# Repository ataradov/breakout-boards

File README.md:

## Breakout Boards

This is a collection of random breakout boards I developed to get started with a new device.

Firmware for the SAM D11 used as a debugger/VCP interface on some boards is available [here](https://github.com/ataradov/free-dap))

### Currrently available boards:

* Atmel SAME70 / SAMS70
* ST STM32G071
* GigaDevice GD32F407V (will probably work for STM32F407 as well)
* Lattice LCMXO256C
* Lattice LCMXO2-2000HC
* Nuvoton M484SIDAE
* Atmel SAMD11 USB Test Board
* Atmel SAMD11 Nano - full breakout with USB connector
* Raspberry Pi RP2040
* Gowin GW1N-UV9QN48

### Errata

The boards are added here at the same time they are submitted for fabrication. There may be issues with them,
but I will not know about them until the boards arrive. Those issues will not be fixed in the files, unless
the boards are really broken and I need to reorder them, or I want to reorder them for some other reason.

Below is a list of known issues:
1. GD32F407V - BOOT0 (pin 94) should be pulled down by a 10 kOhm resistor. This is an easy fix, there is a groud pour near the jumper.
2. SAMD11 USB Test Board - Switch footprint is slightly off (mounting pads are wider than on a real switch).

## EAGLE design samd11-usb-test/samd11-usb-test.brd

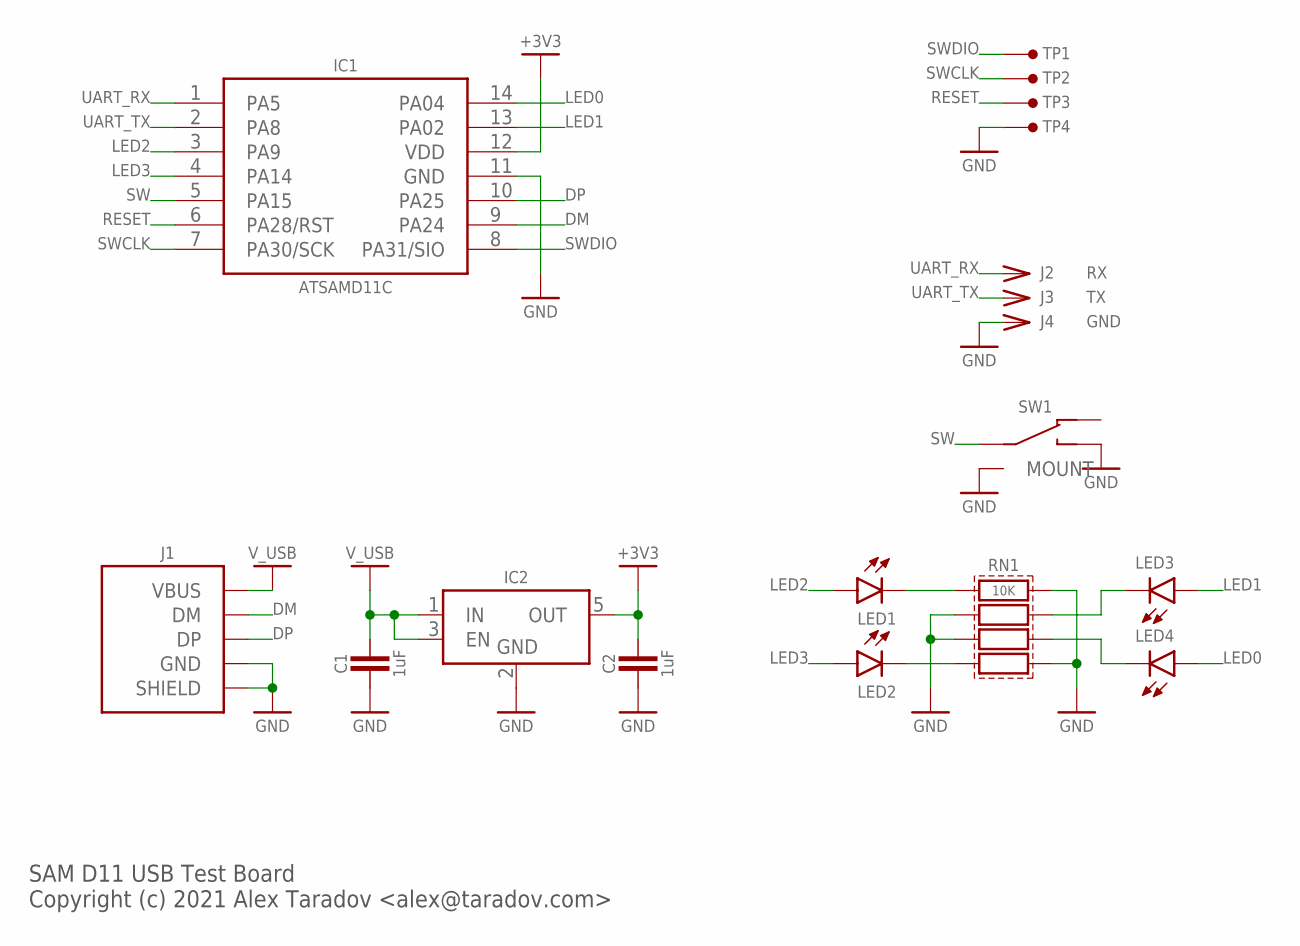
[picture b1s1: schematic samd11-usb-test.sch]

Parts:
C1, C2: 1uF; SMD0603
IC1: ATSAMD11C; SO-14
IC2: MIC5504-SOT23-5; SOT23-5
J1: USB-A-PLUG-TH-NM
J2: RX; PIN-TH
J3: TX; PIN-TH
J4: GND; PIN-TH
LED1, LED2, LED3, LED4: LED_SMDLED_0603; SMD0603
RN1: 10K; SMD0603-X4
SW1: SPDT_SWITCH-MOUNT-SMD-MOUNT-NO-HOLES; SPDT-SMD-5MM-NO-HOLES
TP1, TP2, TP3, TP4: TEST-POINT-1.27MM-TH; TP-1.27MM-TH

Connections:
+3V3: C2.2, IC1.12 (VDD), IC2.5 (OUT)
DM: IC1.9 (PA24), J1.2 (DM)
DP: IC1.10 (PA25), J1.3 (DP)
GND: C1.1, C2.1, IC1.11 (GND), IC2.2 (GND), J1.4 (GND), J1.M1 (SHIELD), J1.M2 (SHIELD), J4.1, RN1.2, RN1.3, RN1.5, RN1.8, SW1.B, SW1.M0 (MOUNT), SW1.M1 (MOUNT), SW1.M2 (MOUNT), SW1.M3 (MOUNT), TP4.1
LED0: IC1.14 (PA04), LED4.1 (A)
LED1: IC1.13 (PA02), LED3.1 (A)
LED2: IC1.3 (PA9), LED1.1 (A)
LED3: IC1.4 (PA14), LED2.1 (A)
unnamed: LED2.2 (C), RN1.4
unnamed: LED1.2 (C), RN1.1
unnamed: LED3.2 (C), RN1.7
unnamed: LED4.2 (C), RN1.6
RESET: IC1.6 (PA28/RST), TP3.1
SW: IC1.5 (PA15), SW1.C
SWCLK: IC1.7 (PA30/SCK), TP2.1
SWDIO: IC1.8 (PA31/SIO), TP1.1
UART_RX: IC1.1 (PA5), J2.1
UART_TX: IC1.2 (PA8), J3.1
V_USB: C1.2, IC2.1 (IN), IC2.3 (EN), J1.1 (VBUS)

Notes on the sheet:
SAM D11 USB Test Board Copyright (c) 2021 Alex Taradov <alex@taradov.com>

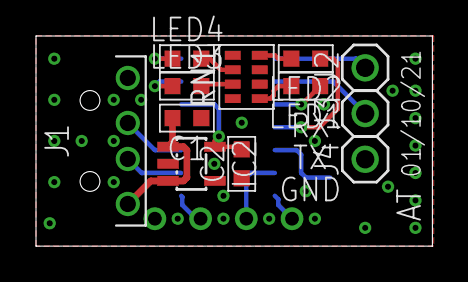
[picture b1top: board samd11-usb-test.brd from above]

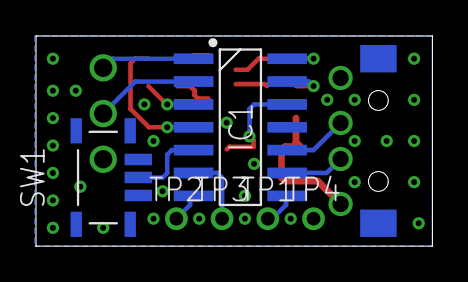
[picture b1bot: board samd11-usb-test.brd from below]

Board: 2 copper layers, 22.0 x 11.7 mm, 18 parts (6 on the bottom side), 19 nets.

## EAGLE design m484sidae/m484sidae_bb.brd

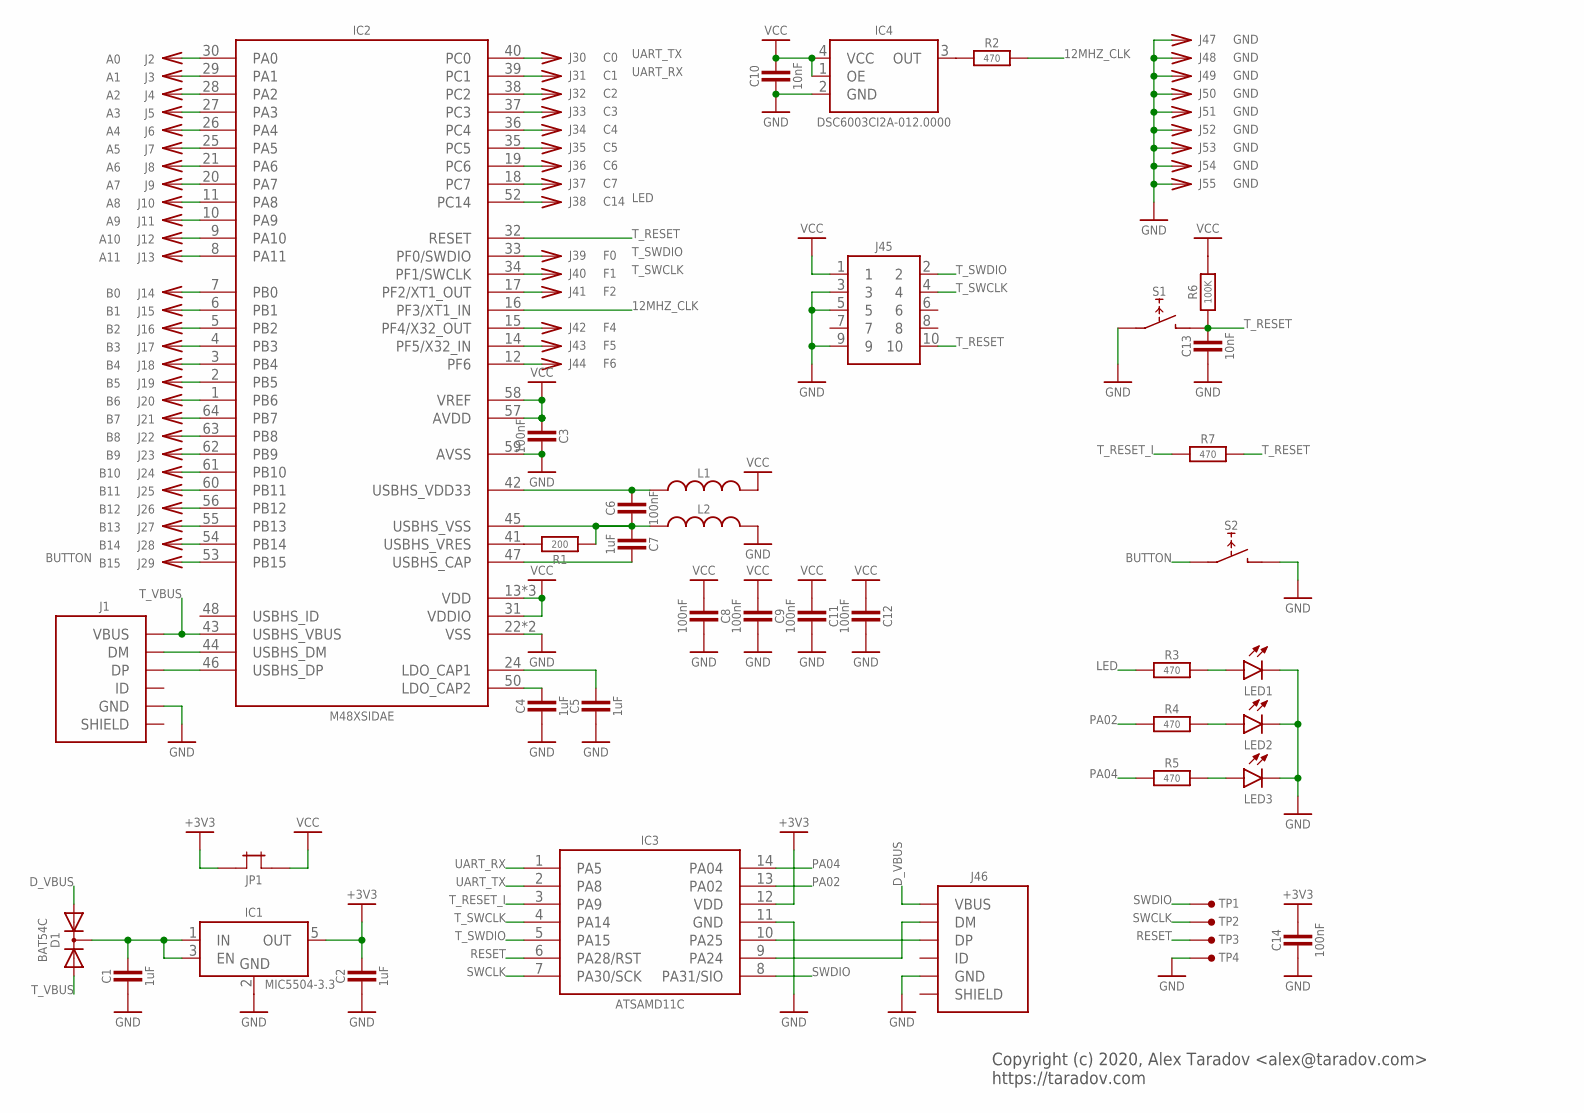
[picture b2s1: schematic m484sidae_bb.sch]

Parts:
C1, C2, C4, C5, C7: 1uF; SMD0603
C3, C6, C8, C9, C11, C12, C14: 100nF; SMD0603
C10, C13: 10nF; SMD0603
D1: BAT54C; SOT23
IC1: MIC5504-3.3; SOT23-5
IC2: M48XSIDAE; TQFP-64-0.4MM
IC3: ATSAMD11C; SO-14
IC4: DSC6003CI2A-012.0000; CDFN4
J1, J46: USB-B-MICRO-SMT; USB-B-MICRO-SMT-SHELL-TH
J2: A0; PIN-TH
J3: A1; PIN-TH
J4: A2; PIN-TH
J5: A3; PIN-TH
J6: A4; PIN-TH
J7: A5; PIN-TH
J8: A6; PIN-TH
J9: A7; PIN-TH
J10: A8; PIN-TH
J11: A9; PIN-TH
J12: A10; PIN-TH
J13: A11; PIN-TH
J14: B0; PIN-TH
J15: B1; PIN-TH
J16: B2; PIN-TH
J17: B3; PIN-TH
J18: B4; PIN-TH
J19: B5; PIN-TH
J20: B6; PIN-TH
J21: B7; PIN-TH
J22: B8; PIN-TH
J23: B9; PIN-TH
J24: B10; PIN-TH
J25: B11; PIN-TH
J26: B12; PIN-TH
J27: B13; PIN-TH
J28: B14; PIN-TH
J29: B15; PIN-TH
J30: C0; PIN-TH
J31: C1; PIN-TH
J32: C2; PIN-TH
J33: C3; PIN-TH
J34: C4; PIN-TH
J35: C5; PIN-TH
J36: C6; PIN-TH
J37: C7; PIN-TH
J38: C14; PIN-TH
J39: F0; PIN-TH
J40: F1; PIN-TH
J41: F2; PIN-TH
J42: F4; PIN-TH
J43: F5; PIN-TH
J44: F6; PIN-TH
J45: HEADER-5X2-TH-1.27; HEADER-5X2-1.27MM
J47, J48, J49, J50, J51, J52, J53, J54, J55: GND; PIN-TH
JP1: JUMPER-TH-TH; JUMPER-TH
L1, L2: L-0603; SMD0603
LED1, LED2, LED3: LED_SMDLED_0603; SMD0603
R1: 200; SMD0603
R2, R3, R4, R5, R7: 470; SMD0603
R6: 100K; SMD0603
S1, S2: TACT_SWITCH_6MM-SMD-HALF; TACT-SMD-6MM-HALF
TP1: SIO; TP-1.27MM
TP2, TP3, TP4: TEST-POINT-1.27MM; TP-1.27MM

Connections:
12MHZ_CLK: IC2.16 (PF3/XT1_IN), R2.2
+3V3: C2.2, C14.2, IC1.5 (OUT), IC3.12 (VDD), JP1.1
BUTTON: IC2.53 (PB15), J29.1, S2.1
D_VBUS: D1.1 (A1), J46.1 (VBUS)
GND: C1.1, C2.1, C3.2, C4.1, C5.1, C8.2, C9.2, C10.1, C11.2, C12.2, C13.1, C14.1, IC1.2 (GND), IC2.22 (VSS), IC2.49 (VSS), IC2.59 (AVSS), IC3.11 (GND), IC4.2 (GND), J1.5 (GND), J45.3, J45.5, J45.9, J46.5 (GND), J47.1, J48.1, J49.1, J50.1, J51.1, J52.1, J53.1, J54.1, J55.1, L2.2, LED1.2 (C), LED2.2 (C), LED3.2 (C), S1.1, S2.2, TP4.1
IN: C1.2, D1.3 (CC), IC1.1 (IN), IC1.3 (EN)
LED: IC2.52 (PC14), J38.1, R3.1
unnamed: IC3.9 (PA24), J46.2 (DM)
unnamed: IC3.10 (PA25), J46.3 (DP)
unnamed: LED2.1 (A), R4.2
unnamed: IC4.3 (OUT), R2.1
unnamed: LED3.1 (A), R5.2
unnamed: IC2.44 (USBHS_DM), J1.2 (DM)
unnamed: IC2.46 (USBHS_DP), J1.3 (DP)
unnamed: IC2.41 (USBHS_VRES), R1.2
unnamed: C5.2, IC2.24 (LDO_CAP1)
unnamed: C4.2, IC2.50 (LDO_CAP2)
unnamed: LED1.1 (A), R3.2
unnamed: IC2.37 (PC3), J33.1
unnamed: IC2.38 (PC2), J32.1
unnamed: IC2.36 (PC4), J34.1
unnamed: IC2.35 (PC5), J35.1
unnamed: IC2.19 (PC6), J36.1
unnamed: IC2.18 (PC7), J37.1
unnamed: IC2.30 (PA0), J2.1
unnamed: IC2.29 (PA1), J3.1
unnamed: IC2.28 (PA2), J4.1
unnamed: IC2.27 (PA3), J5.1
unnamed: IC2.26 (PA4), J6.1
unnamed: IC2.25 (PA5), J7.1
unnamed: IC2.21 (PA6), J8.1
unnamed: IC2.20 (PA7), J9.1
unnamed: IC2.10 (PA9), J11.1
unnamed: IC2.9 (PA10), J12.1
unnamed: IC2.8 (PA11), J13.1
unnamed: IC2.11 (PA8), J10.1
unnamed: IC2.7 (PB0), J14.1
unnamed: IC2.6 (PB1), J15.1
unnamed: IC2.5 (PB2), J16.1
unnamed: IC2.4 (PB3), J17.1
unnamed: IC2.3 (PB4), J18.1
unnamed: IC2.1 (PB6), J20.1
unnamed: IC2.64 (PB7), J21.1
unnamed: IC2.63 (PB8), J22.1
unnamed: IC2.62 (PB9), J23.1
unnamed: IC2.61 (PB10), J24.1
unnamed: IC2.60 (PB11), J25.1
unnamed: IC2.56 (PB12), J26.1
unnamed: IC2.55 (PB13), J27.1
unnamed: IC2.54 (PB14), J28.1
unnamed: IC2.2 (PB5), J19.1
unnamed: IC2.17 (PF2/XT1_OUT), J41.1
unnamed: IC2.12 (PF6), J44.1
unnamed: IC2.15 (PF4/X32_OUT), J42.1
unnamed: IC2.14 (PF5/X32_IN), J43.1
PA02: IC3.13 (PA02), R4.1
PA04: IC3.14 (PA04), R5.1
RESET: IC3.6 (PA28/RST), TP3.1
SWCLK: IC3.7 (PA30/SCK), TP2.1
SWDIO: IC3.8 (PA31/SIO), TP1.1
T_RESET: C13.2, IC2.32 (RESET), J45.10, R6.1, R7.2, S1.2
T_RESET_I: IC3.3 (PA9), R7.1
T_SWCLK: IC2.34 (PF1/SWCLK), IC3.4 (PA14), J40.1, J45.4
T_SWDIO: IC2.33 (PF0/SWDIO), IC3.5 (PA15), J39.1, J45.2
T_VBUS: D1.2 (A2), IC2.43 (USBHS_VBUS), J1.1 (VBUS)
UART_RX: IC2.39 (PC1), IC3.1 (PA5), J31.1
UART_TX: IC2.40 (PC0), IC3.2 (PA8), J30.1
USBHS_CAP: C7.2, IC2.47 (USBHS_CAP)
USBHS_GND: C6.1, C7.1, IC2.45 (USBHS_VSS), L2.1, R1.1
USBHS_VDD33: C6.2, IC2.42 (USBHS_VDD33), L1.1
VCC: C3.1, C8.1, C9.1, C10.2, C11.1, C12.1, IC2.13 (VDD), IC2.23 (VDD), IC2.31 (VDDIO), IC2.51 (VDD), IC2.57 (AVDD), IC2.58 (VREF), IC4.1 (OE), IC4.4 (VCC), J45.1, JP1.2, L1.2, R6.2

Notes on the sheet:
Copyright (c) 2020, Alex Taradov <alex@taradov.com> https://taradov.com

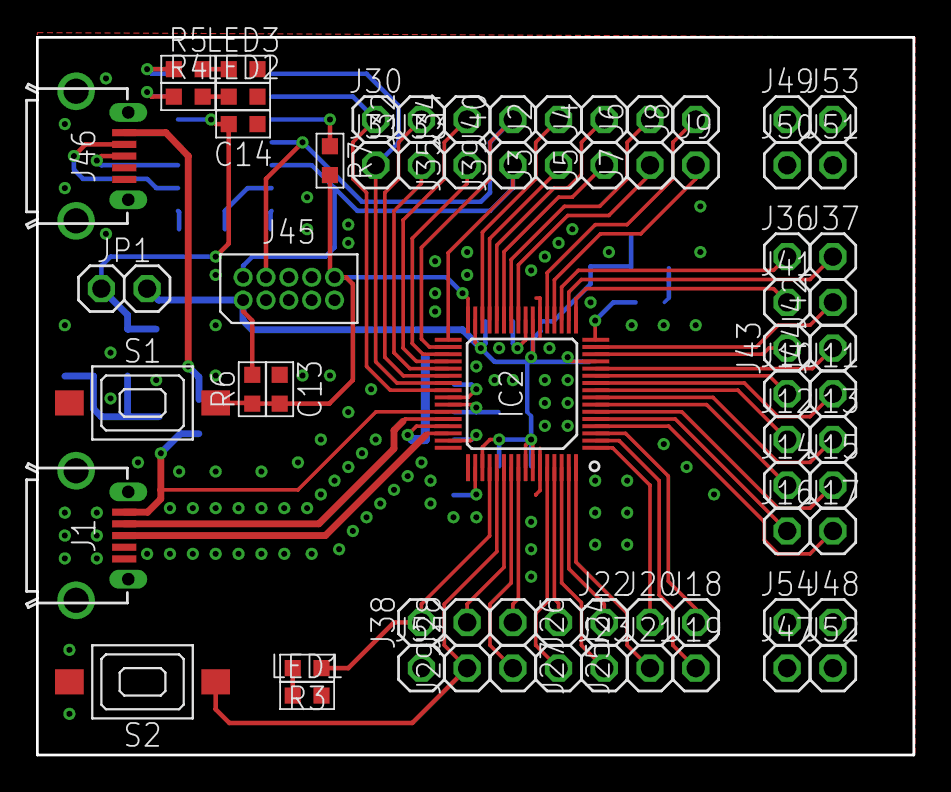
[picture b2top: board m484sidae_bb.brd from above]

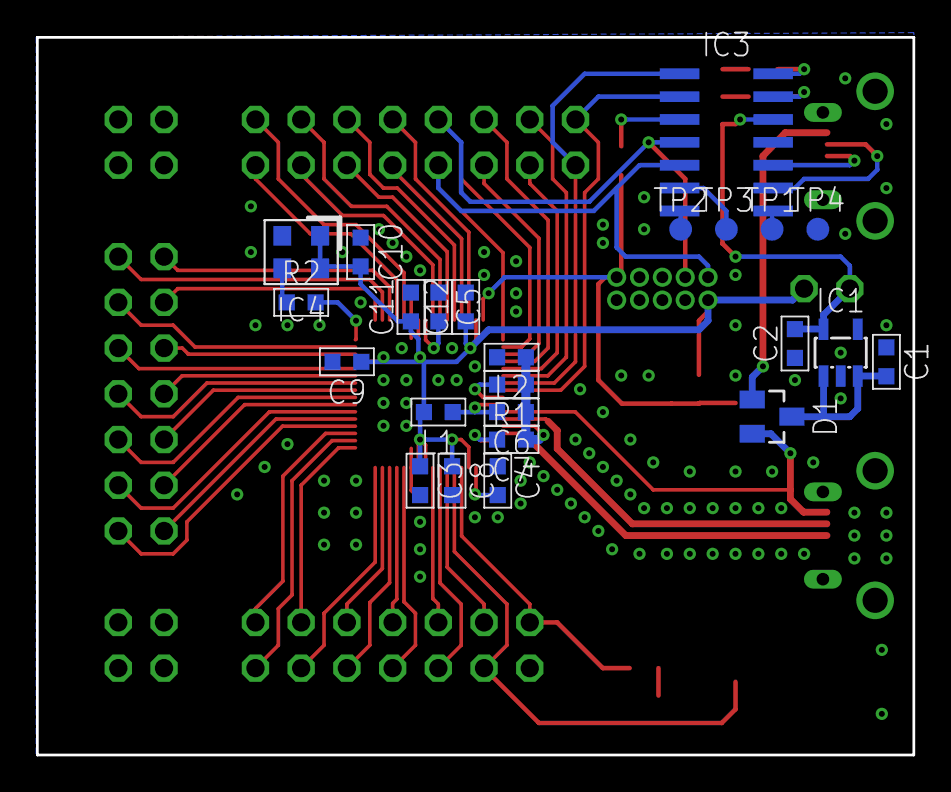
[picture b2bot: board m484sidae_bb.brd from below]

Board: 2 copper layers, 48.7 x 39.9 mm, 93 parts (24 on the bottom side), 71 nets.

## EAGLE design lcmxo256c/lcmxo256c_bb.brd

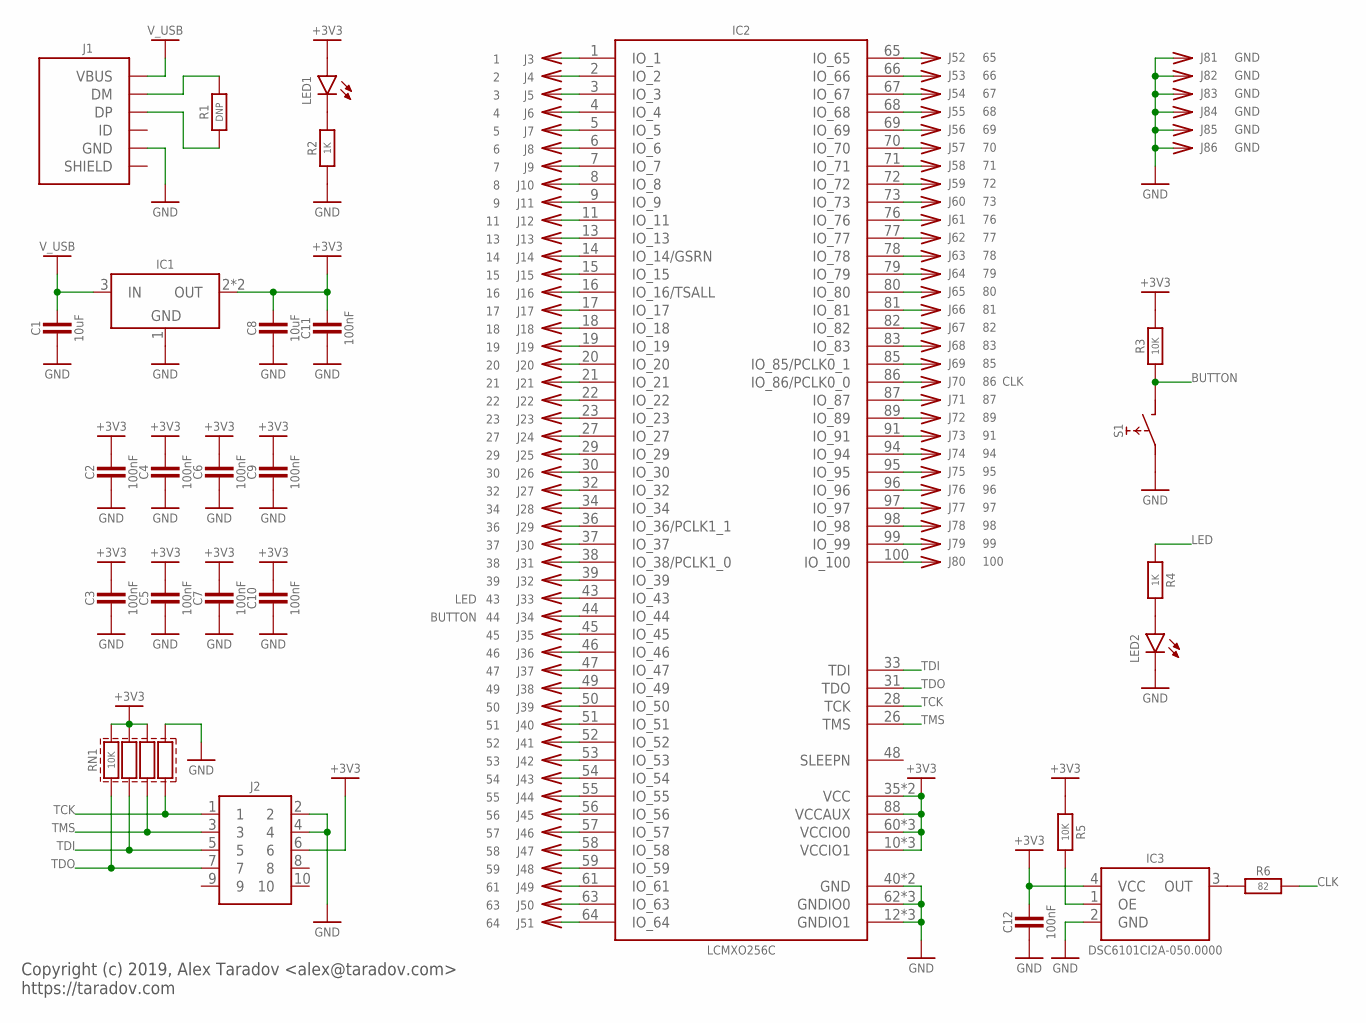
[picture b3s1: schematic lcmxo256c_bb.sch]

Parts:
C1, C8: 10uF; SMD0805
C2, C3, C4, C5, C6, C7, C9, C10, C11, C12: 100nF; SMD0603
IC1: LM1117-SOT223; SOT223
IC2: LCMXO256C; TQFP-100-0.5MM
IC3: DSC6101CI2A-050.0000; CDFN4
J1: USB-B-MICRO-SMT; USB-B-MICRO-SMT-SHELL-TH
J2: HEADER-5X2-TH-1.27; HEADER-5X2-1.27MM
J3: 1; PIN-TH
J4: 2; PIN-TH
J5: 3; PIN-TH
J6: 4; PIN-TH
J7: 5; PIN-TH
J8: 6; PIN-TH
J9: 7; PIN-TH
J10: 8; PIN-TH
J11: 9; PIN-TH
J12: 11; PIN-TH
J13: 13; PIN-TH
J14: 14; PIN-TH
J15: 15; PIN-TH
J16: 16; PIN-TH
J17: 17; PIN-TH
J18: 18; PIN-TH
J19: 19; PIN-TH
J20: 20; PIN-TH
J21: 21; PIN-TH
J22: 22; PIN-TH
J23: 23; PIN-TH
J24: 27; PIN-TH
J25: 29; PIN-TH
J26: 30; PIN-TH
J27: 32; PIN-TH
J28: 34; PIN-TH
J29: 36; PIN-TH
J30: 37; PIN-TH
J31: 38; PIN-TH
J32: 39; PIN-TH
J33: 43; PIN-TH
J34: 44; PIN-TH
J35: 45; PIN-TH
J36: 46; PIN-TH
J37: 47; PIN-TH
J38: 49; PIN-TH
J39: 50; PIN-TH
J40: 51; PIN-TH
J41: 52; PIN-TH
J42: 53; PIN-TH
J43: 54; PIN-TH
J44: 55; PIN-TH
J45: 56; PIN-TH
J46: 57; PIN-TH
J47: 58; PIN-TH
J48: 59; PIN-TH
J49: 61; PIN-TH
J50: 63; PIN-TH
J51: 64; PIN-TH
J52: 65; PIN-TH
J53: 66; PIN-TH
J54: 67; PIN-TH
J55: 68; PIN-TH
J56: 69; PIN-TH
J57: 70; PIN-TH
J58: 71; PIN-TH
J59: 72; PIN-TH
J60: 73; PIN-TH
J61: 76; PIN-TH
J62: 77; PIN-TH
J63: 78; PIN-TH
J64: 79; PIN-TH
J65: 80; PIN-TH
J66: 81; PIN-TH
J67: 82; PIN-TH
J68: 83; PIN-TH
J69: 85; PIN-TH
J70: 86; PIN-TH
J71: 87; PIN-TH
J72: 89; PIN-TH
J73: 91; PIN-TH
J74: 94; PIN-TH
J75: 95; PIN-TH
J76: 96; PIN-TH
J77: 97; PIN-TH
J78: 98; PIN-TH
J79: 99; PIN-TH
J80: 100; PIN-TH
J81, J82, J83, J84, J85, J86: GND; PIN-TH
LED1, LED2: LED_SMDLED_0603; SMD0603
R1: DNP; SMD0603
R2, R4: 1K; SMD0603
R3, R5: 10K; SMD0603
R6: 82; SMD0603
RN1: 10K; SMD0603-X4
S1: TACT_SWITCH_6MM-SMD-HALF; TACT-SMD-6MM-HALF

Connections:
+3V3: C2.2, C3.2, C4.2, C5.2, C6.2, C7.2, C8.2, C9.2, C10.2, C11.2, C12.2, IC1.2 (OUT), IC1.4 (OUT), IC2.10 (VCCIO1), IC2.24 (VCCIO1), IC2.35 (VCC), IC2.41 (VCCIO1), IC2.60 (VCCIO0), IC2.74 (VCCIO0), IC2.88 (VCCAUX), IC2.90 (VCC), IC2.92 (VCCIO0), IC3.4 (VCC), J2.6, LED1.1 (A), R3.2, R5.1, RN1.6, RN1.7, RN1.8
BUTTON: IC2.44 (IO_44), J34.1, R3.1, S1.2
CLK: IC2.86 (IO_86/PCLK0_0), J70.1, R6.2
GND: C1.1, C2.1, C3.1, C4.1, C5.1, C6.1, C7.1, C8.1, C9.1, C10.1, C11.1, C12.1, IC1.1 (GND), IC2.12 (GNDIO1), IC2.25 (GNDIO1), IC2.40 (GND), IC2.42 (GNDIO1), IC2.62 (GNDIO0), IC2.75 (GNDIO0), IC2.84 (GND), IC2.93 (GNDIO0), IC3.2 (GND), J1.5 (GND), J2.2, J2.4, J81.1, J82.1, J83.1, J84.1, J85.1, J86.1, LED2.2 (C), R2.1, RN1.5, S1.1
LED: IC2.43 (IO_43), J33.1, R4.1
unnamed: IC2.1 (IO_1), J3.1
unnamed: IC2.2 (IO_2), J4.1
unnamed: IC2.3 (IO_3), J5.1
unnamed: J1.2 (DM), R1.2
unnamed: IC2.4 (IO_4), J6.1
unnamed: J1.3 (DP), R1.1
unnamed: IC2.5 (IO_5), J7.1
unnamed: IC2.6 (IO_6), J8.1
unnamed: IC2.7 (IO_7), J9.1
unnamed: IC2.8 (IO_8), J10.1
unnamed: IC2.9 (IO_9), J11.1
unnamed: IC2.11 (IO_11), J12.1
unnamed: IC2.13 (IO_13), J13.1
unnamed: IC2.14 (IO_14/GSRN), J14.1
unnamed: IC2.15 (IO_15), J15.1
unnamed: IC2.16 (IO_16/TSALL), J16.1
unnamed: IC2.17 (IO_17), J17.1
unnamed: IC2.18 (IO_18), J18.1
unnamed: IC2.19 (IO_19), J19.1
unnamed: IC2.20 (IO_20), J20.1
unnamed: IC2.21 (IO_21), J21.1
unnamed: IC2.22 (IO_22), J22.1
unnamed: IC2.23 (IO_23), J23.1
unnamed: IC2.27 (IO_27), J24.1
unnamed: IC2.29 (IO_29), J25.1
unnamed: IC2.30 (IO_30), J26.1
unnamed: IC2.32 (IO_32), J27.1
unnamed: IC2.34 (IO_34), J28.1
unnamed: IC2.36 (IO_36/PCLK1_1), J29.1
unnamed: IC2.37 (IO_37), J30.1
unnamed: IC2.38 (IO_38/PCLK1_0), J31.1
unnamed: IC2.39 (IO_39), J32.1
unnamed: IC3.3 (OUT), R6.1
unnamed: IC3.1 (OE), R5.2
unnamed: IC2.45 (IO_45), J35.1
unnamed: IC2.46 (IO_46), J36.1
unnamed: IC2.47 (IO_47), J37.1
unnamed: IC2.49 (IO_49), J38.1
unnamed: IC2.50 (IO_50), J39.1
unnamed: IC2.51 (IO_51), J40.1
unnamed: IC2.52 (IO_52), J41.1
unnamed: IC2.53 (IO_53), J42.1
unnamed: IC2.54 (IO_54), J43.1
unnamed: IC2.55 (IO_55), J44.1
unnamed: IC2.56 (IO_56), J45.1
unnamed: IC2.57 (IO_57), J46.1
unnamed: IC2.58 (IO_58), J47.1
unnamed: IC2.59 (IO_59), J48.1
unnamed: IC2.67 (IO_67), J54.1
unnamed: IC2.61 (IO_61), J49.1
unnamed: IC2.68 (IO_68), J55.1
unnamed: LED2.1 (A), R4.2
unnamed: IC2.63 (IO_63), J50.1
unnamed: IC2.64 (IO_64), J51.1
unnamed: IC2.65 (IO_65), J52.1
unnamed: IC2.66 (IO_66), J53.1
unnamed: IC2.69 (IO_69), J56.1
unnamed: IC2.70 (IO_70), J57.1
unnamed: IC2.71 (IO_71), J58.1
unnamed: IC2.72 (IO_72), J59.1
unnamed: IC2.73 (IO_73), J60.1
unnamed: IC2.76 (IO_76), J61.1
unnamed: IC2.77 (IO_77), J62.1
unnamed: IC2.78 (IO_78), J63.1
unnamed: IC2.79 (IO_79), J64.1
unnamed: IC2.80 (IO_80), J65.1
unnamed: IC2.81 (IO_81), J66.1
unnamed: IC2.82 (IO_82), J67.1
unnamed: IC2.83 (IO_83), J68.1
unnamed: IC2.85 (IO_85/PCLK0_1), J69.1
unnamed: IC2.87 (IO_87), J71.1
unnamed: IC2.89 (IO_89), J72.1
unnamed: IC2.91 (IO_91), J73.1
unnamed: IC2.94 (IO_94), J74.1
unnamed: IC2.95 (IO_95), J75.1
unnamed: IC2.96 (IO_96), J76.1
unnamed: IC2.97 (IO_97), J77.1
unnamed: IC2.98 (IO_98), J78.1
unnamed: IC2.99 (IO_99), J79.1
unnamed: IC2.100 (IO_100), J80.1
unnamed: LED1.2 (C), R2.2
TCK: IC2.28 (TCK), J2.1, RN1.4
TDI: IC2.33 (TDI), J2.5, RN1.2
TDO: IC2.31 (TDO), J2.7, RN1.1
TMS: IC2.26 (TMS), J2.3, RN1.3
V_USB: C1.2, IC1.3 (IN), J1.1 (VBUS)

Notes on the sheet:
Copyright (c) 2019, Alex Taradov <alex@taradov.com> https://taradov.com

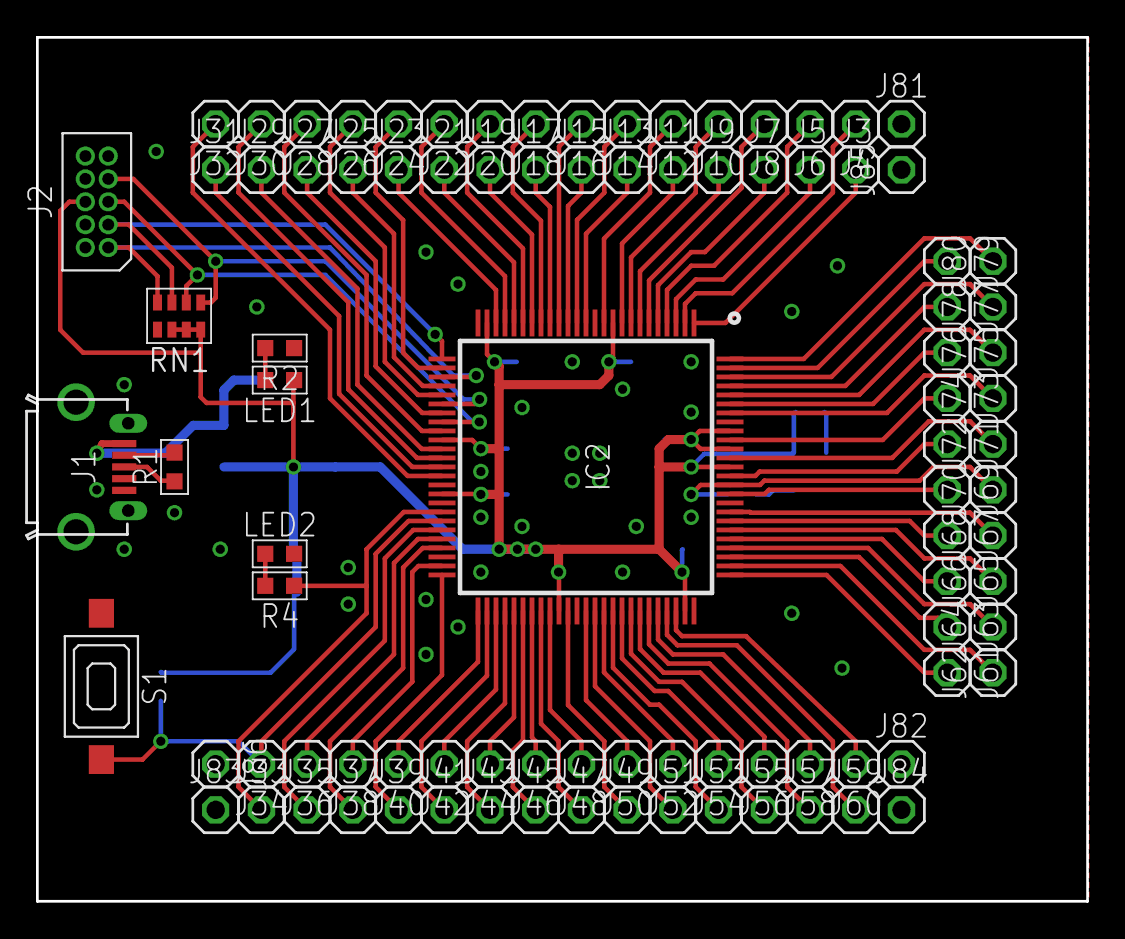
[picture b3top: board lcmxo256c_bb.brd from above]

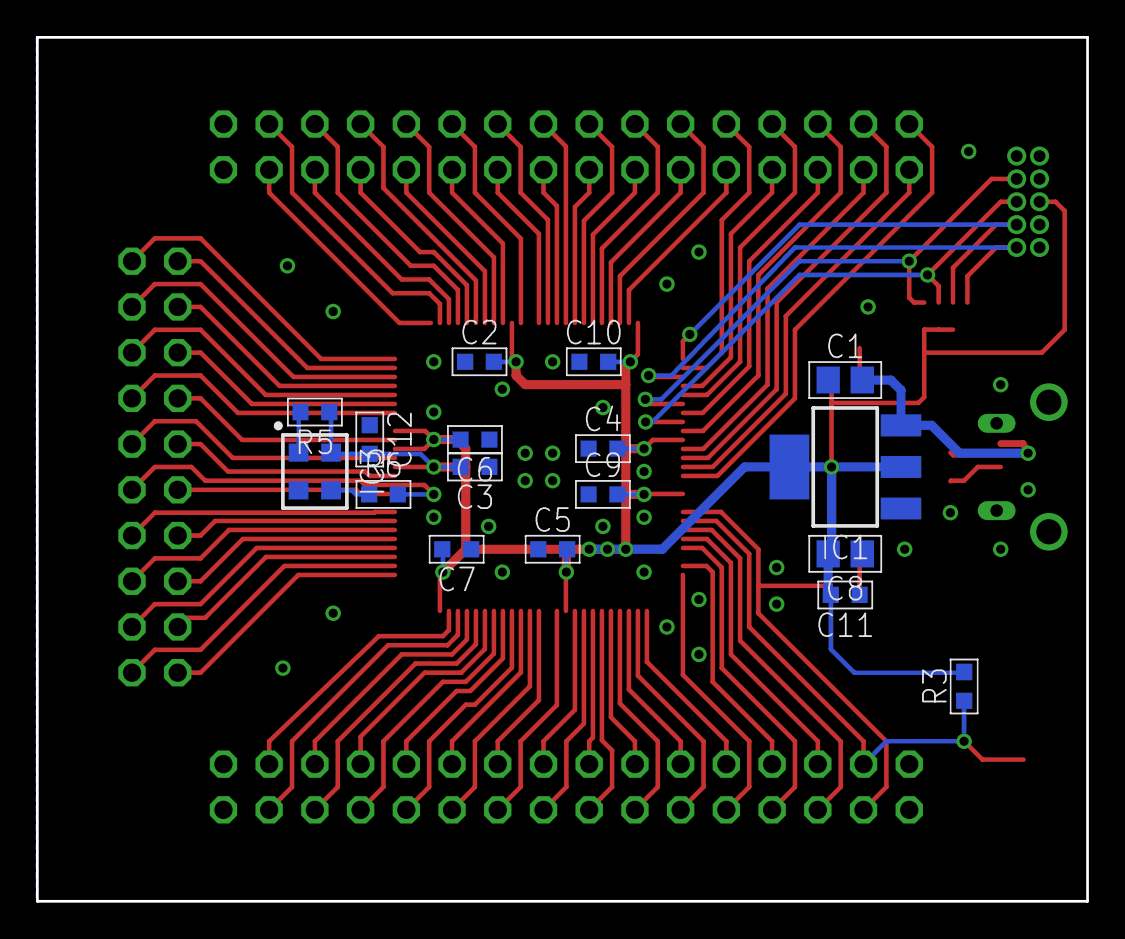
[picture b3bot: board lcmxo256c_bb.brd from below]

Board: 2 copper layers, 58.3 x 48.0 mm, 111 parts (17 on the bottom side), 91 nets.

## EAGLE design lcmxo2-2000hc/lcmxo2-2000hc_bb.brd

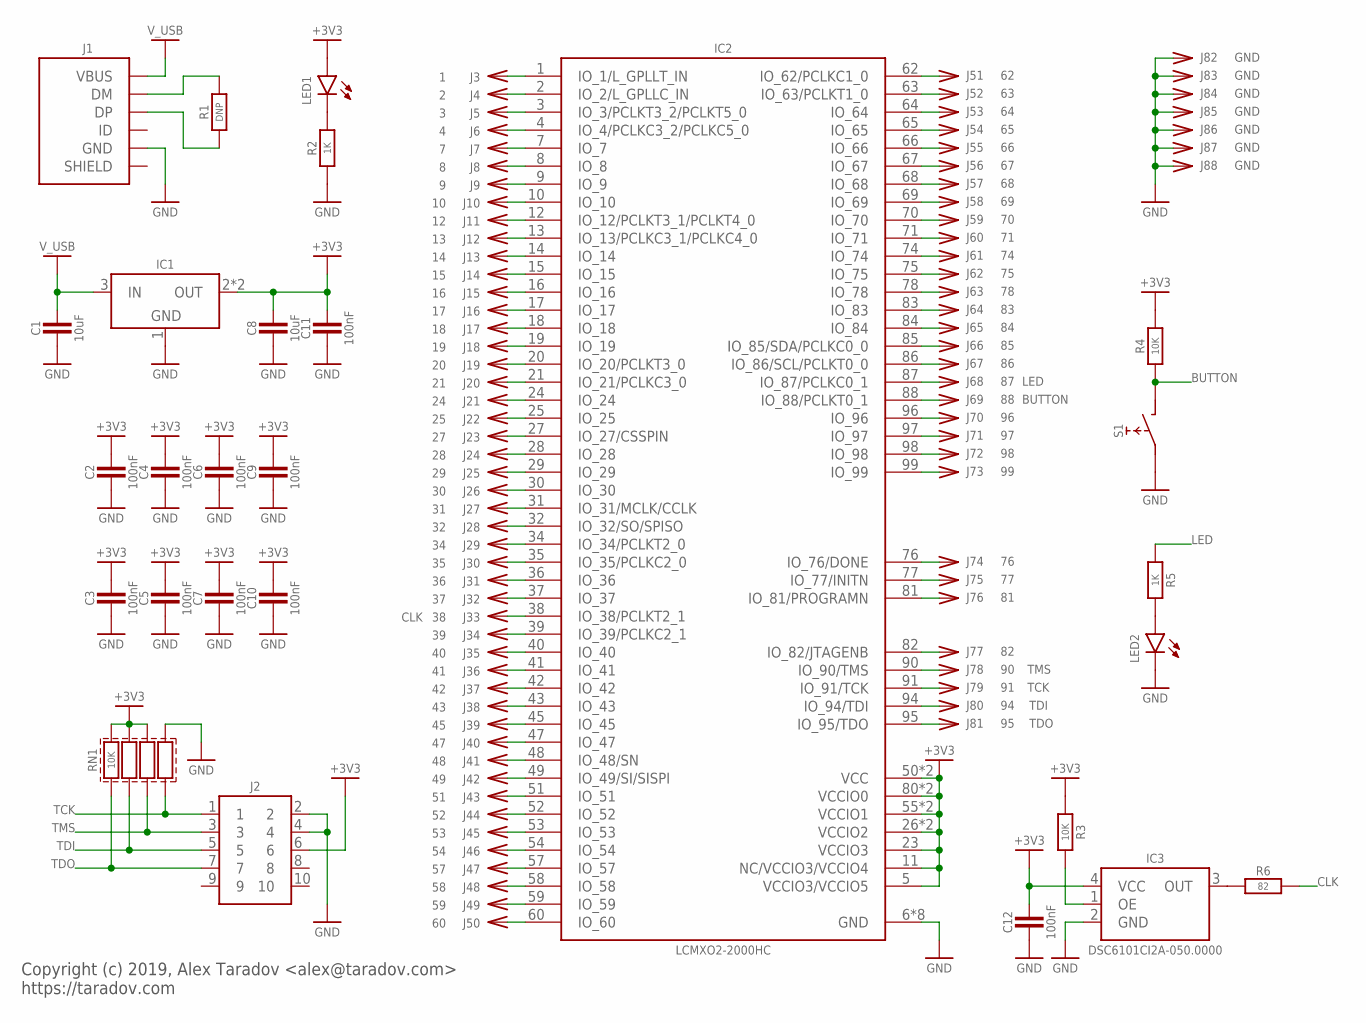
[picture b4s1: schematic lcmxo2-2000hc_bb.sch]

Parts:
C1, C8: 10uF; SMD0805
C2, C3, C4, C5, C6, C7, C9, C10, C11, C12: 100nF; SMD0603
IC1: LM1117-SOT223; SOT223
IC2: LCMXO2-2000HC; TQFP-100-0.5MM
IC3: DSC6101CI2A-050.0000; CDFN4
J1: USB-B-MICRO-SMT; USB-B-MICRO-SMT-SHELL-TH
J2: HEADER-5X2-TH-1.27; HEADER-5X2-1.27MM
J3: 1; PIN-TH
J4: 2; PIN-TH
J5: 3; PIN-TH
J6: 4; PIN-TH
J7: 7; PIN-TH
J8: 8; PIN-TH
J9: 9; PIN-TH
J10: 10; PIN-TH
J11: 12; PIN-TH
J12: 13; PIN-TH
J13: 14; PIN-TH
J14: 15; PIN-TH
J15: 16; PIN-TH
J16: 17; PIN-TH
J17: 18; PIN-TH
J18: 19; PIN-TH
J19: 20; PIN-TH
J20: 21; PIN-TH
J21: 24; PIN-TH
J22: 25; PIN-TH
J23: 27; PIN-TH
J24: 28; PIN-TH
J25: 29; PIN-TH
J26: 30; PIN-TH
J27: 31; PIN-TH
J28: 32; PIN-TH
J29: 34; PIN-TH
J30: 35; PIN-TH
J31: 36; PIN-TH
J32: 37; PIN-TH
J33: 38; PIN-TH
J34: 39; PIN-TH
J35: 40; PIN-TH
J36: 41; PIN-TH
J37: 42; PIN-TH
J38: 43; PIN-TH
J39: 45; PIN-TH
J40: 47; PIN-TH
J41: 48; PIN-TH
J42: 49; PIN-TH
J43: 51; PIN-TH
J44: 52; PIN-TH
J45: 53; PIN-TH
J46: 54; PIN-TH
J47: 57; PIN-TH
J48: 58; PIN-TH
J49: 59; PIN-TH
J50: 60; PIN-TH
J51: 62; PIN-TH
J52: 63; PIN-TH
J53: 64; PIN-TH
J54: 65; PIN-TH
J55: 66; PIN-TH
J56: 67; PIN-TH
J57: 68; PIN-TH
J58: 69; PIN-TH
J59: 70; PIN-TH
J60: 71; PIN-TH
J61: 74; PIN-TH
J62: 75; PIN-TH
J63: 78; PIN-TH
J64: 83; PIN-TH
J65: 84; PIN-TH
J66: 85; PIN-TH
J67: 86; PIN-TH
J68: 87; PIN-TH
J69: 88; PIN-TH
J70: 96; PIN-TH
J71: 97; PIN-TH
J72: 98; PIN-TH
J73: 99; PIN-TH
J74: 76; PIN-TH
J75: 77; PIN-TH
J76: 81; PIN-TH
J77: 82; PIN-TH
J78: 90; PIN-TH
J79: 91; PIN-TH
J80: 94; PIN-TH
J81: 95; PIN-TH
J82, J83, J84, J85, J86, J87, J88: GND; PIN-TH
LED1, LED2: LED_SMDLED_0603; SMD0603
R1: DNP; SMD0603
R2, R5: 1K; SMD0603
R3, R4: 10K; SMD0603
R6: 82; SMD0603
RN1: 10K; SMD0603-X4
S1: TACT_SWITCH_6MM-SMD-HALF; TACT-SMD-6MM-HALF

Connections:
+3V3: C2.2, C3.2, C4.2, C5.2, C6.2, C7.2, C8.2, C9.2, C10.2, C11.2, C12.2, IC1.2 (OUT), IC1.4 (OUT), IC2.5 (VCCIO3/VCCIO5), IC2.11 (NC/VCCIO3/VCCIO4), IC2.23 (VCCIO3), IC2.26 (VCCIO2), IC2.46 (VCCIO2), IC2.50 (VCC), IC2.55 (VCCIO1), IC2.73 (VCCIO1), IC2.80 (VCCIO0), IC2.93 (VCCIO0), IC2.100 (VCC), IC3.4 (VCC), J2.6, LED1.1 (A), R3.1, R4.2, RN1.6, RN1.7, RN1.8
BUTTON: IC2.88 (IO_88/PCLKT0_1), J69.1, R4.1, S1.2
CLK: IC2.38 (IO_38/PCLKT2_1), J33.1, R6.2
GND: C1.1, C2.1, C3.1, C4.1, C5.1, C6.1, C7.1, C8.1, C9.1, C10.1, C11.1, C12.1, IC1.1 (GND), IC2.6 (GND), IC2.22 (GND), IC2.33 (GND), IC2.44 (GND), IC2.56 (GND), IC2.72 (GND), IC2.79 (GND), IC2.92 (GND), IC3.2 (GND), J1.5 (GND), J2.2, J2.4, J82.1, J83.1, J84.1, J85.1, J86.1, J87.1, J88.1, LED2.2 (C), R2.1, RN1.5, S1.1
JTAGEN: IC2.82 (IO_82/JTAGENB), J77.1
LED: IC2.87 (IO_87/PCLKC0_1), J68.1, R5.1
unnamed: IC2.1 (IO_1/L_GPLLT_IN), J3.1
unnamed: IC2.2 (IO_2/L_GPLLC_IN), J4.1
unnamed: IC2.3 (IO_3/PCLKT3_2/PCLKT5_0), J5.1
unnamed: J1.2 (DM), R1.2
unnamed: IC2.4 (IO_4/PCLKC3_2/PCLKC5_0), J6.1
unnamed: J1.3 (DP), R1.1
unnamed: IC2.7 (IO_7), J7.1
unnamed: IC2.8 (IO_8), J8.1
unnamed: IC2.9 (IO_9), J9.1
unnamed: IC2.10 (IO_10), J10.1
unnamed: IC2.12 (IO_12/PCLKT3_1/PCLKT4_0), J11.1
unnamed: IC2.13 (IO_13/PCLKC3_1/PCLKC4_0), J12.1
unnamed: IC2.14 (IO_14), J13.1
unnamed: IC2.15 (IO_15), J14.1
unnamed: IC2.16 (IO_16), J15.1
unnamed: IC2.17 (IO_17), J16.1
unnamed: IC2.18 (IO_18), J17.1
unnamed: IC2.19 (IO_19), J18.1
unnamed: IC2.20 (IO_20/PCLKT3_0), J19.1
unnamed: IC2.21 (IO_21/PCLKC3_0), J20.1
unnamed: IC2.24 (IO_24), J21.1
unnamed: IC2.25 (IO_25), J22.1
unnamed: IC2.27 (IO_27/CSSPIN), J23.1
unnamed: IC2.28 (IO_28), J24.1
unnamed: IC2.29 (IO_29), J25.1
unnamed: IC2.30 (IO_30), J26.1
unnamed: IC2.31 (IO_31/MCLK/CCLK), J27.1
unnamed: IC2.32 (IO_32/SO/SPISO), J28.1
unnamed: IC2.34 (IO_34/PCLKT2_0), J29.1
unnamed: IC2.35 (IO_35/PCLKC2_0), J30.1
unnamed: IC2.36 (IO_36), J31.1
unnamed: IC2.37 (IO_37), J32.1
unnamed: IC3.3 (OUT), R6.1
unnamed: IC3.1 (OE), R3.2
unnamed: IC2.39 (IO_39/PCLKC2_1), J34.1
unnamed: IC2.40 (IO_40), J35.1
unnamed: IC2.41 (IO_41), J36.1
unnamed: IC2.42 (IO_42), J37.1
unnamed: IC2.43 (IO_43), J38.1
unnamed: IC2.45 (IO_45), J39.1
unnamed: IC2.47 (IO_47), J40.1
unnamed: IC2.48 (IO_48/SN), J41.1
unnamed: IC2.49 (IO_49/SI/SISPI), J42.1
unnamed: IC2.51 (IO_51), J43.1
unnamed: IC2.52 (IO_52), J44.1
unnamed: IC2.53 (IO_53), J45.1
unnamed: IC2.54 (IO_54), J46.1
unnamed: IC2.57 (IO_57), J47.1
unnamed: IC2.58 (IO_58), J48.1
unnamed: IC2.59 (IO_59), J49.1
unnamed: LED2.1 (A), R5.2
unnamed: IC2.60 (IO_60), J50.1
unnamed: IC2.62 (IO_62/PCLKC1_0), J51.1
unnamed: IC2.63 (IO_63/PCLKT1_0), J52.1
unnamed: IC2.99 (IO_99), J73.1
unnamed: IC2.98 (IO_98), J72.1
unnamed: IC2.64 (IO_64), J53.1
unnamed: IC2.65 (IO_65), J54.1
unnamed: IC2.66 (IO_66), J55.1
unnamed: IC2.67 (IO_67), J56.1
unnamed: IC2.68 (IO_68), J57.1
unnamed: IC2.69 (IO_69), J58.1
unnamed: IC2.70 (IO_70), J59.1
unnamed: IC2.71 (IO_71), J60.1
unnamed: IC2.74 (IO_74), J61.1
unnamed: IC2.75 (IO_75), J62.1
unnamed: IC2.78 (IO_78), J63.1
unnamed: IC2.83 (IO_83), J64.1
unnamed: IC2.84 (IO_84), J65.1
unnamed: IC2.85 (IO_85/SDA/PCLKC0_0), J66.1
unnamed: IC2.86 (IO_86/SCL/PCLKT0_0), J67.1
unnamed: IC2.96 (IO_96), J70.1
unnamed: IC2.97 (IO_97), J71.1
unnamed: IC2.76 (IO_76/DONE), J74.1
unnamed: IC2.77 (IO_77/INITN), J75.1
unnamed: IC2.81 (IO_81/PROGRAMN), J76.1
unnamed: LED1.2 (C), R2.2
TCK: IC2.91 (IO_91/TCK), J2.1, J79.1, RN1.4
TDI: IC2.94 (IO_94/TDI), J2.5, J80.1, RN1.2
TDO: IC2.95 (IO_95/TDO), J2.7, J81.1, RN1.1
TMS: IC2.90 (IO_90/TMS), J2.3, J78.1, RN1.3
V_USB: C1.2, IC1.3 (IN), J1.1 (VBUS)

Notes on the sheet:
Copyright (c) 2019, Alex Taradov <alex@taradov.com> https://taradov.com

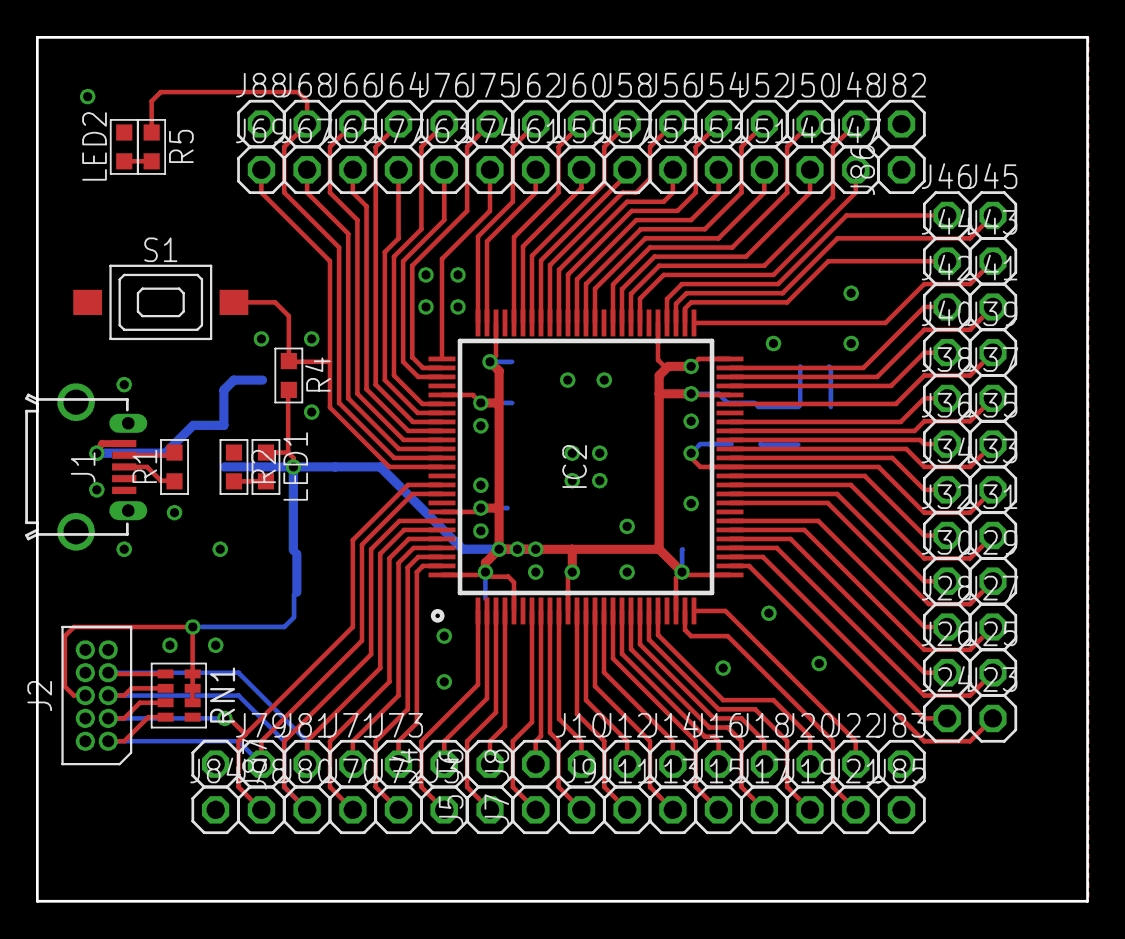
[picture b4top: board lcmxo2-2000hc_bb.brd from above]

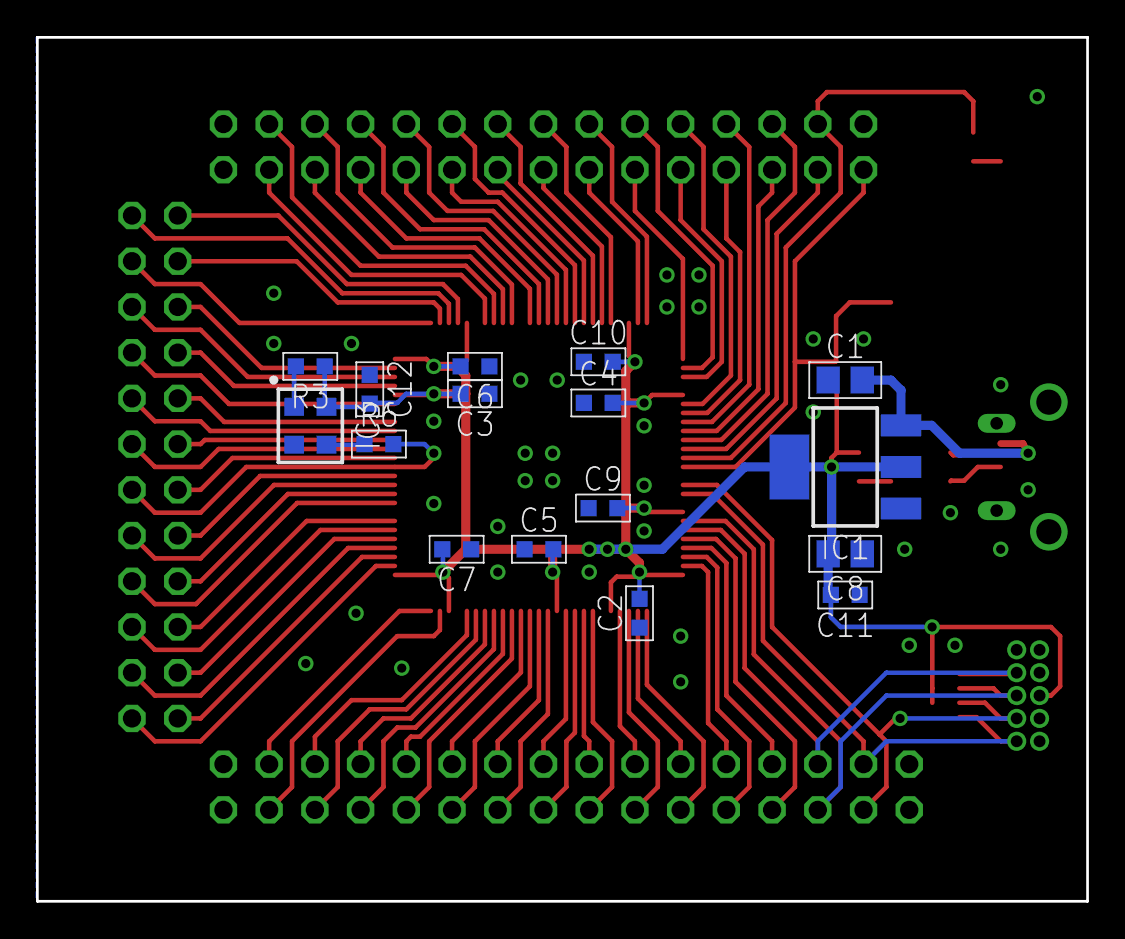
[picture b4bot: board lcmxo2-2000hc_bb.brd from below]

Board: 2 copper layers, 58.3 x 48.0 mm, 113 parts (16 on the bottom side), 88 nets.
